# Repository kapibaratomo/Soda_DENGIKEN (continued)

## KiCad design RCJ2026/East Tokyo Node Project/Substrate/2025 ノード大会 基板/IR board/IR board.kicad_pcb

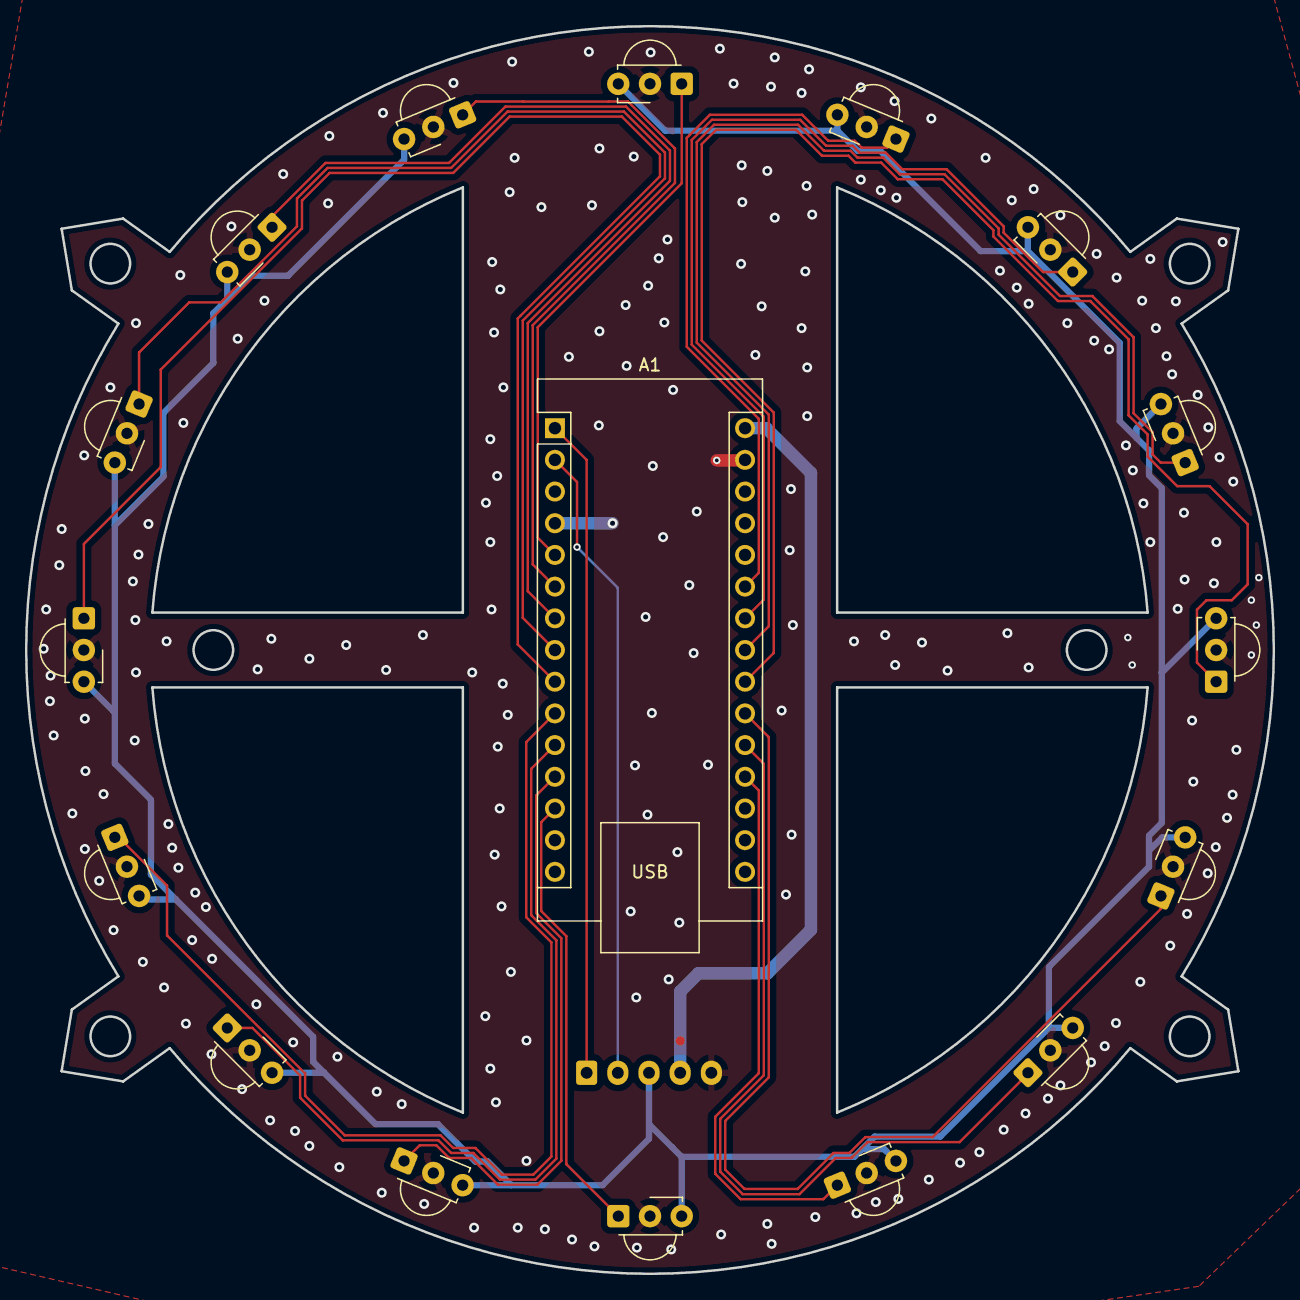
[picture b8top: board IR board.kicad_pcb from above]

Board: 2 copper layers, 100.0 x 100.0 mm, 18 parts (1 on the bottom side), 21 nets.

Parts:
A1: Arduino_Nano_Every; Arduino_Nano
J1: Conn_01x05_Socket; JST_XH_B5B-XH-A_1x05_P2.50mm_Vertical
U1, U2, U3, U4, U5, U6, U7, U8, U9, U10, U11, U12, U13, U14, U15, U16: TSSP58038; Vishay_MINICAST-3Pin

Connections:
+3.3V: J1.3, U1.3 (Vs), U2.3 (Vs), U3.3 (Vs), U4.3 (Vs), U5.3 (Vs), U6.3 (Vs), U7.3 (Vs), U8.3 (Vs), U9.3 (Vs), U10.3 (Vs), U11.3 (Vs), U12.3 (Vs), U13.3 (Vs), U14.3 (Vs), U15.3 (Vs), U16.3 (Vs)
+9V: A1.30 (VIN), J1.4
GND: A1.4 (GND), A1.29 (GND), J1.5, U1.2 (GND), U2.2 (GND), U3.2 (GND), U4.2 (GND), U5.2 (GND), U6.2 (GND), U7.2 (GND), U8.2 (GND), U9.2 (GND), U10.2 (GND), U11.2 (GND), U12.2 (GND), U13.2 (GND), U14.2 (GND), U15.2 (GND), U16.2 (GND)
IR 0: A1.5 (D2), U1.1 (OUT)
IR 1: A1.6 (D3), U2.1 (OUT)
IR 2: A1.7 (D4), U3.1 (OUT)
IR 3: A1.8 (D5), U4.1 (OUT)
IR 4: A1.9 (D6), U5.1 (OUT)
IR 5: A1.10 (D7), U6.1 (OUT)
IR 6: A1.11 (D8), U7.1 (OUT)
IR 7: A1.12 (D9), U8.1 (OUT)
IR 8: A1.13 (D10), U9.1 (OUT)
IR 9: A1.19 (A0), U10.1 (OUT)
IR 10: A1.20 (A1), U11.1 (OUT)
IR 11: A1.21 (A2), U12.1 (OUT)
IR 12: A1.22 (A3), U13.1 (OUT)
IR 13: A1.23 (SDA/A4), U14.1 (OUT)
IR 14: A1.24 (SCL/A5), U15.1 (OUT)
IR 15: A1.25 (A6), U16.1 (OUT)
IR RX: A1.2 (RX1), J1.2
IR TX: A1.1 (TX1), J1.1

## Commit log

2026-02-18 無視リストを更新してゴミを除外
2026-02-18 予算書の更新と不要ファイルの削除
2026-02-18 Auto Backup: 2026/02/18 17:54:50.34
2026-02-18 Auto Backup: 2026/02/18 17:58:34.81
2026-02-18 Auto Backup: 2026/02/18 18:11:18.50
2026-02-18 Auto Backup: 2026/02/18 21:42:58.30
2026-02-19 Auto Backup: 2026/02/19 16:07:46.02
2026-02-19 Auto Backup: 2026/02/19 16:55:47.94
2026-02-19 Auto Backup: 2026/02/19 18:25:14.96
2026-02-19 Auto Backup: 2026/02/19 21:04:39.45
2026-02-19 Auto Backup: 2026/02/19 21:06:09.95
2026-02-20 Auto Backup: 2026/02/20 17:29:36.08
2026-02-20 Auto Backup: 2026/02/20 17:31:11.78
2026-02-20 Auto Backup: 2026/02/20 17:52:59.18
2026-02-20 Auto Backup: 2026/02/20 17:53:21.11
2026-03-09 Auto Backup: 2026/03/09 13:07:55.49
2026-03-09 Auto Backup: 2026/03/09 16:26:29.90
2026-03-11 Auto Backup: 2026/03/11 17:25:39.27
2026-03-11 Auto Backup: 2026/03/11 18:28:48.37
2026-03-13 Auto Backup: 2026/03/13 15:37:30.72
2026-03-17 Auto Backup: 2026/03/17 12:46:45.54
2026-03-17 Auto Backup: 2026/03/17 14:43:41.44
2026-03-17 5個のフォルダをgit管理から除外
2026-03-17 Auto Backup: 2026/03/17 15:25:52.59
2026-03-17 全フォルダを個人リポジトリに追加
2026-03-17 サブモジュール解除・ファイルとして追加
2026-03-17 git_bak削除・kicadライブラリ追加
2026-03-17 kicadライブラリ追加・gitignore修正
2026-03-17 Auto Backup: 2026/03/17 20:28:42.29
2026-03-24 Auto Backup: 2026/03/24 15:00:23.58
2026-03-27 Auto Backup: 2026/03/27 19:50:55.14
2026-04-04 Auto Backup: 2026/04/04 20:53:02.03
2026-04-13 Auto Backup: 2026/04/13 16:29:43.37
2026-04-18 Auto Backup: 2026/04/18 18:20:52.35
2026-04-21 Auto Backup: 2026/04/21 20:53:26.04
2026-04-24 Auto Backup: 2026/04/24 21:18:25.90
2026-04-24 Auto Backup: 2026/04/24 21:20:37.59
2026-04-24 Auto Backup: 2026/04/24 21:22:48.80
2026-04-27 force resync
2026-04-27 reset files
2026-04-27 reupload files
2026-04-29 Auto Backup: 2026/04/29 12:14:26.80
2026-04-29 Auto Backup: 2026/04/29 12:16:17.07
2026-04-29 Auto Backup: 2026/04/29 12:17:35.47
2026-04-29 Auto Backup: 2026/04/29 17:42:26.28
2026-04-30 Auto Backup: 2026/04/30 15:52:33.50
